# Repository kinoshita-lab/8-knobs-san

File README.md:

# 8-knobs-san kit

[Document in Japanese](README_ja.md)
## PCB board with 8 Potentiometers

8-knobs-san is a handy PCB with 8 potentiometers and analog multiplexer.
You can connect another 8-knobs-san PCB with same GPIOs, by switching /Enable pin with builtin inverter.

## Kit contents

- Pre-assembled circuit board
- 1x7 pin socket

## How to assemble

Solder the included 1x7 pin socket into the following place below:

## Sample program

Please refer to the software/exapmle <https://github.com/kinoshita-lab/8-knobs-san/tree/main/software/example>

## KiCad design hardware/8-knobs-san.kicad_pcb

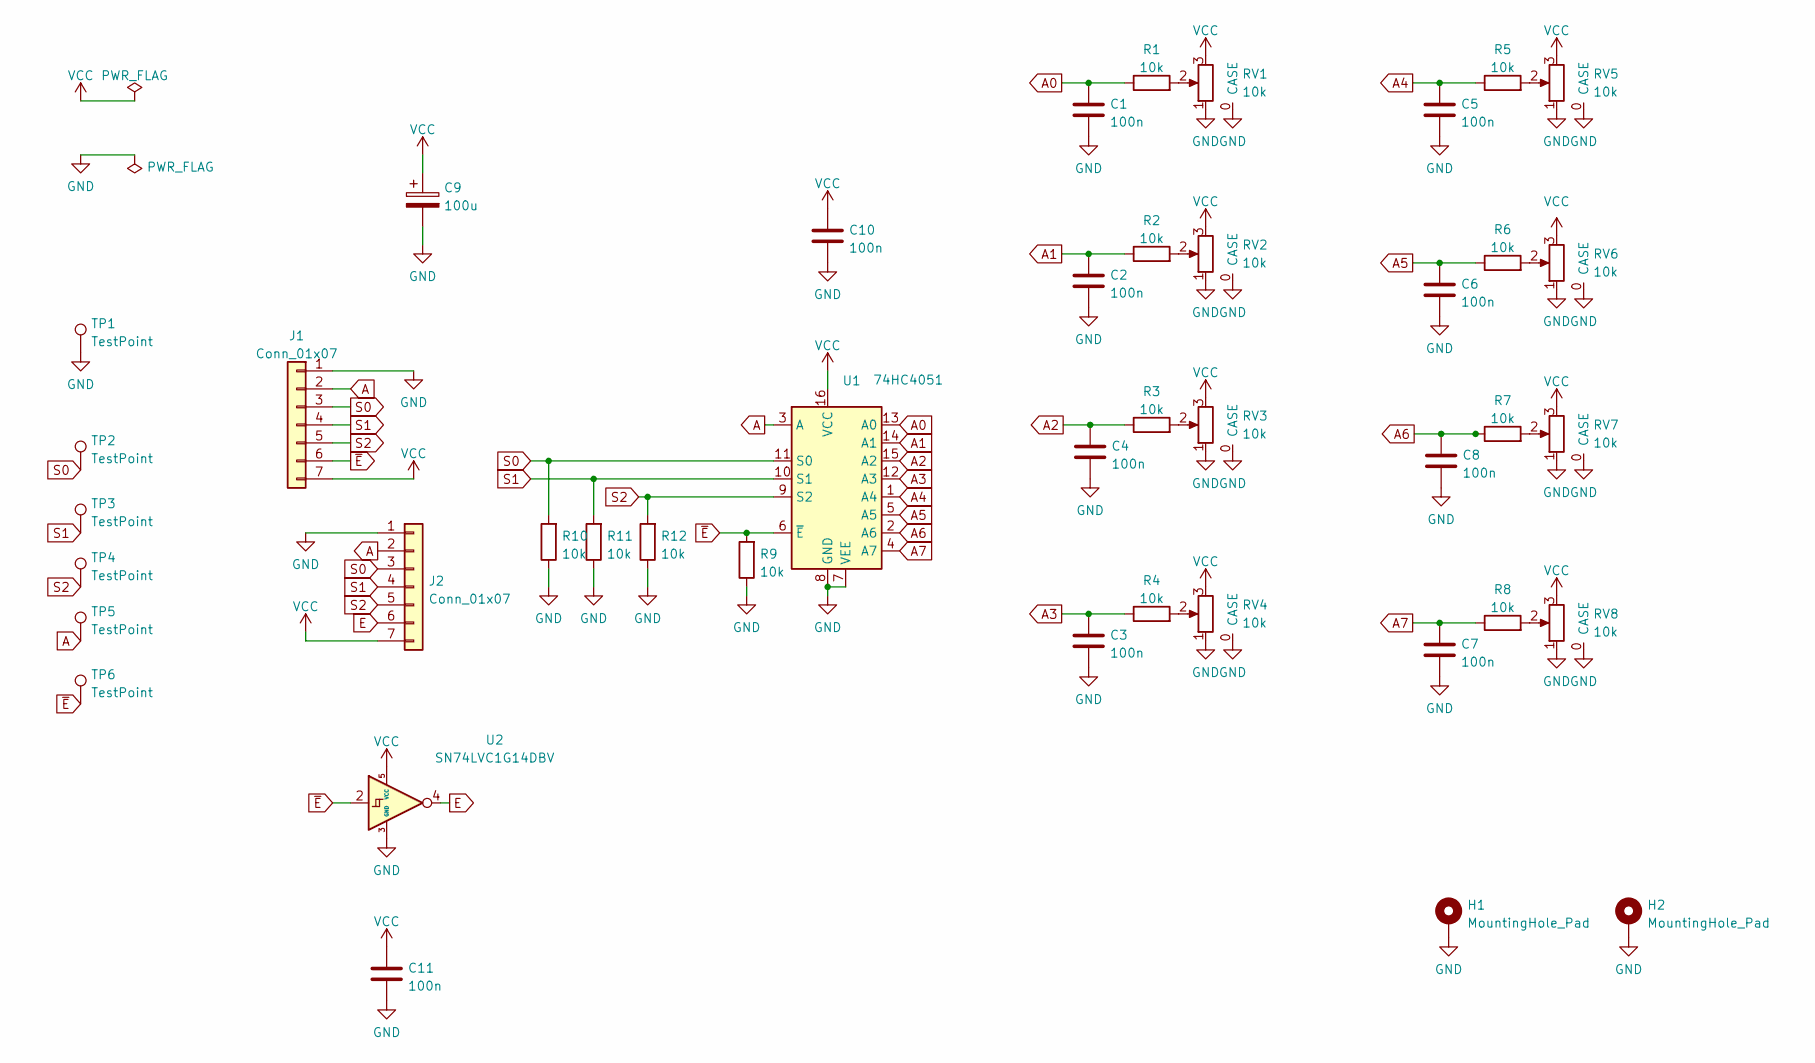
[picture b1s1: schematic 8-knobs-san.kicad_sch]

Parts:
C1, C2, C3, C4, C5, C6, C7, C8, C10, C11: 100n; C_0402_1005Metric; LCSC C1525
C9: 100u; CP_Elec_6.3x5.4_Nichicon; LCSC C111600
H1, H2: MountingHole_Pad; MountingHole_3.2mm_M3_DIN965_Pad
J1, J2: Conn_01x07; PinHeader_1x07_P2.54mm_Vertical
R1, R2, R3, R4, R5, R6, R7, R8, R9, R10, R11, R12: 10k; R_0402_1005Metric_Pad0.72x0.64mm_HandSolder; LCSC C25744
RV1, RV2, RV3, RV4, RV5, RV6, RV7, RV8: 10k; Potentiometer_Alps_RK09K_Horizontal_CORRECTED; LCSC C209779
TP1, TP2, TP3, TP4, TP5, TP6: TestPoint; TestPoint_THTPad_D2.0mm_Drill1.0mm
U1: 74HC4051; TSSOP-16_4.4x5mm_P0.65mm; LCSC C5645
U2: SN74LVC1G14DBV; SOT-23-5

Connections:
A: J1.2, J2.2, TP5.1, U1.3 (A)
A0: C1.1, R1.1, U1.13 (A0)
A1: C2.1, R2.1, U1.14 (A1)
A2: C4.1, R3.1, U1.15 (A2)
A3: C3.1, R4.1, U1.12 (A3)
A4: C5.1, R5.1, U1.1 (A4)
A5: C6.1, R6.1, U1.5 (A5)
A6: C8.1, R7.1, U1.2 (A6)
A7: C7.1, R8.1, U1.4 (A7)
E: J2.6, U2.4
GND: C1.2, C2.2, C3.2, C4.2, C5.2, C6.2, C7.2, C8.2, C9.2, C10.2, C11.2, H1.1, H2.1, J1.1, J2.1, R9.1, R10.1, R11.1, R12.1, RV1.0 (CASE), RV1.1, RV2.0 (CASE), RV2.1, RV3.0 (CASE), RV3.1, RV4.0 (CASE), RV4.1, RV5.0 (CASE), RV5.1, RV6.0 (CASE), RV6.1, RV7.0 (CASE), RV7.1, RV8.0 (CASE), RV8.1, TP1.1, U1.7 (VEE), U1.8 (GND), U2.3 (GND)
unnamed: R1.2, RV1.2
unnamed: R2.2, RV2.2
unnamed: R3.2, RV3.2
unnamed: R4.2, RV4.2
unnamed: R5.2, RV5.2
unnamed: R6.2, RV6.2
unnamed: R7.2, RV7.2
unnamed: R8.2, RV8.2
S0: J1.3, J2.3, R10.2, TP2.1, U1.11 (S0)
S1: J1.4, J2.4, R11.2, TP3.1, U1.10 (S1)
S2: J1.5, J2.5, R12.2, TP4.1, U1.9 (S2)
VCC: C9.1, C10.1, C11.1, J1.7, J2.7, RV1.3, RV2.3, RV3.3, RV4.3, RV5.3, RV6.3, RV7.3, RV8.3, U1.16 (VCC), U2.5 (VCC)
~E: J1.6, R9.2, TP6.1, U1.6 (~E), U2.2

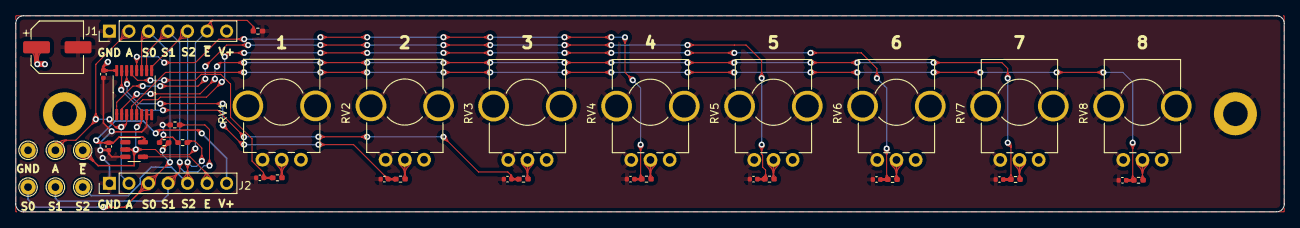
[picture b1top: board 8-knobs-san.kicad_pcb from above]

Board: 2 copper layers, 165.0 x 25.5 mm, 43 parts (0 on the bottom side), 24 nets.

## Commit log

2022-12-21 Add hardware design file
2022-12-21 Add library file and example
2022-12-21 Create LICENSE
2022-12-21 Add docs
2022-12-21 modify docs
